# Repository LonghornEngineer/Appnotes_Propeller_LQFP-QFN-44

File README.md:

***
###Appnotes_Propeller_LQFP-QFN-44
***
**Dual footprint for the P8X32A-Q44 and P8X32A-M44 32-bit MCU.**

The Parallax Propeller MCU runs in 3 different flavors. A DIP-40 package (P8X32A-D40), a LQFP-44 package (P8X32A-Q44), and a QFN-44 package (P8X32A-M44). This appnote covers the two SMD packages; LQFP-44 and QFN-44.

See [here for more information](http://longhornengineer.com/2014/01/01/appnote-parallax-propeller-layout-dual-smd-footprint/).

***
**License Information**

This project is under the [Creative Commons Attribution-ShareAlike 4.0 International License](LICENSE.md). These files are provided with no warranty and should be used at your own risk. 

***

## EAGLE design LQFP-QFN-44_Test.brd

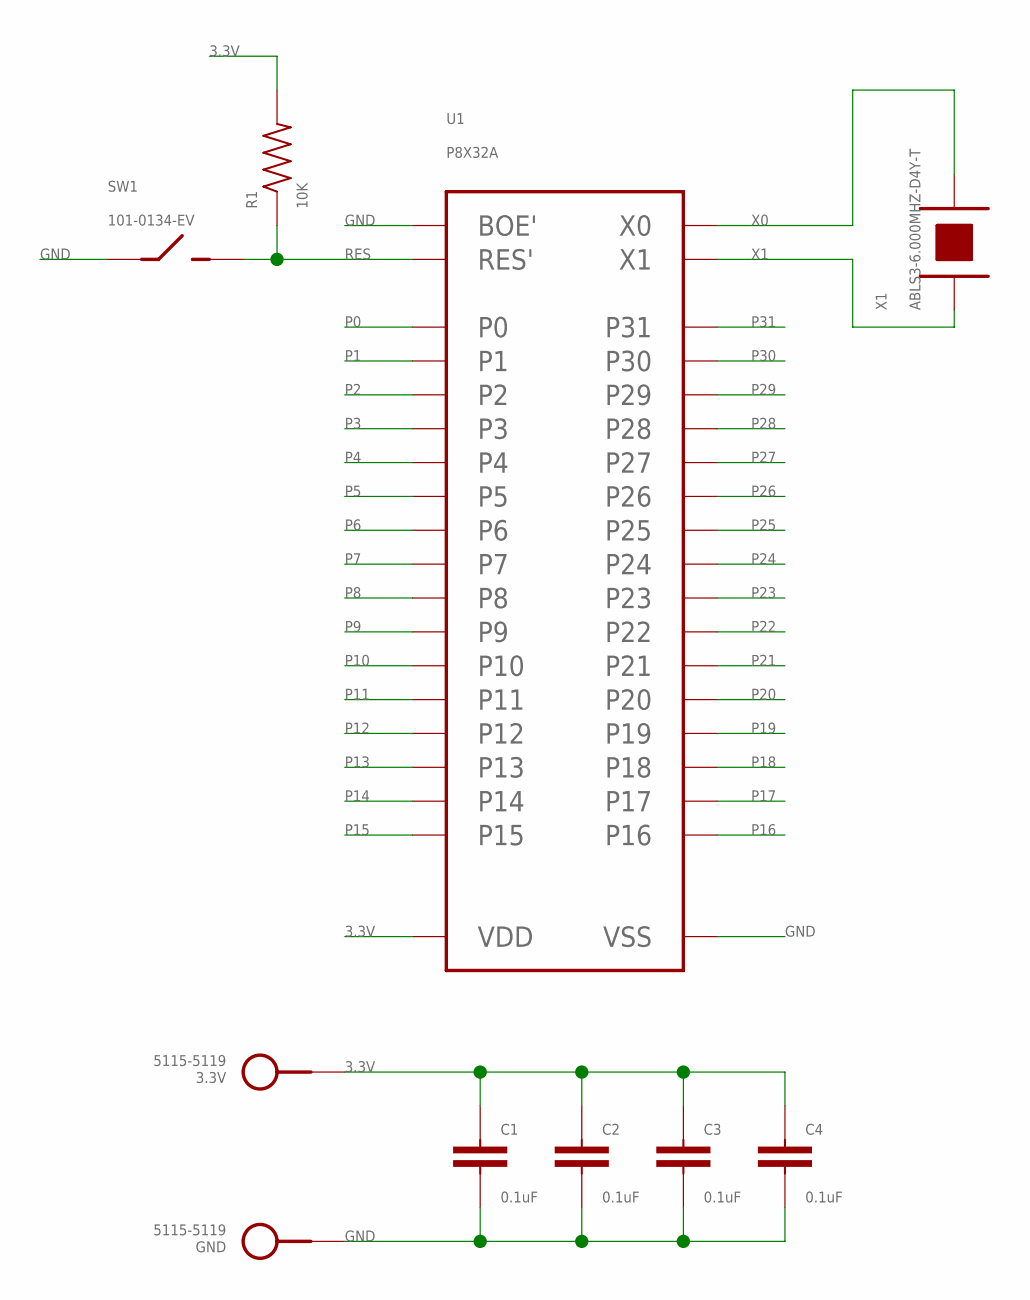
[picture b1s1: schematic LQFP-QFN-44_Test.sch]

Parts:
3.3V: 5115-5119; KEYSTONE_5115-5119
C1, C2, C3, C4: 0.1uF; 0402
GND: 5115-5119; KEYSTONE_5115-5119
R1: 10K; 0402
SW1: 101-0134-EV
U1: P8X32A; DUAL_LQFP_QFN_44
X1: ABLS3-6.000MHZ-D4Y-T; HC-49/US_SM

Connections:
3.3V: 3.3V.P$1, C1.1, C2.1, C3.1, C4.1, R1.2, U1.8 (VDD), U1.18 (VDD), U1.30 (VDD), U1.40 (VDD), U1.52 (VDD), U1.62 (VDD), U1.74 (VDD), U1.84 (VDD)
GND: C1.2, C2.2, C3.2, C4.2, GND.P$1, SW1.1 (A), U1.5 (VSS), U1.6 (BOE'), U1.17 (VSS), U1.27 (VSS), U1.39 (VSS), U1.49 (VSS), U1.50 (BOE'), U1.61 (VSS), U1.71 (VSS), U1.83 (VSS), U1.PAD (VSS)
P0: U1.41 (P0), U1.85 (P0)
P1: U1.42 (P1), U1.86 (P1)
P2: U1.43 (P2), U1.87 (P2)
P3: U1.44 (P3), U1.88 (P3)
P4: U1.1 (P4), U1.45 (P4)
P5: U1.2 (P5), U1.46 (P5)
P6: U1.3 (P6), U1.47 (P6)
P7: U1.4 (P7), U1.48 (P7)
P8: U1.9 (P8), U1.53 (P8)
P9: U1.10 (P9), U1.54 (P9)
P10: U1.11 (P10), U1.55 (P10)
P11: U1.12 (P11), U1.56 (P11)
P12: U1.13 (P12), U1.57 (P12)
P13: U1.14 (P13), U1.58 (P13)
P14: U1.15 (P14), U1.59 (P14)
P15: U1.16 (P15), U1.60 (P15)
P16: U1.19 (P16), U1.63 (P16)
P17: U1.20 (P17), U1.64 (P17)
P18: U1.21 (P18), U1.65 (P18)
P19: U1.22 (P19), U1.66 (P19)
P20: U1.23 (P20), U1.67 (P20)
P21: U1.24 (P21), U1.68 (P21)
P22: U1.25 (P22), U1.69 (P22)
P23: U1.26 (P23), U1.70 (P23)
P24: U1.31 (P24), U1.75 (P24)
P25: U1.32 (P25), U1.76 (P25)
P26: U1.33 (P26), U1.77 (P26)
P27: U1.34 (P27), U1.78 (P27)
P28: U1.35 (P28), U1.79 (P28)
P29: U1.36 (P29), U1.80 (P29)
P30: U1.37 (P30), U1.81 (P30)
P31: U1.38 (P31), U1.82 (P31)
RES: R1.1, SW1.2 (B), U1.7 (RES'), U1.51 (RES')
X0: U1.29 (X0), U1.73 (X0), X1.P$2
X1: U1.28 (X1), U1.72 (X1), X1.P$1

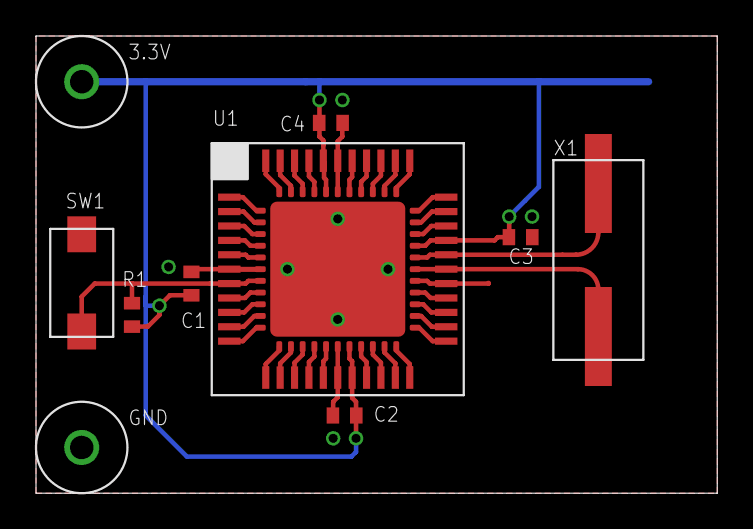
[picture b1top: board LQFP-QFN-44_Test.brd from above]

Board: 2 copper layers, 37.8 x 25.4 mm, 10 parts (0 on the bottom side), 37 nets.

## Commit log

2013-12-31 Pushing first set of files.
2014-01-02 Finished the layout for the appnote.
2014-01-02 Added restrict around X1 on top layer.
2014-01-02 Added Schematic image
2014-01-02 Changed Crystal Value to ABLS3-6.000MHZ-D4Y-T
2014-02-12 Fixed GND trace near XTAL pin.
2014-04-09 Updating License to CC-BY-SA
2014-04-09 Update to CC-BY-SA License.
2016-08-23 updating readme and adding final information.
